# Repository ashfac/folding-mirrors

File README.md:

# Automatic Folding Mirrors schematics in KiCAD
## Schematics

## Board

## PCB

## PCBA

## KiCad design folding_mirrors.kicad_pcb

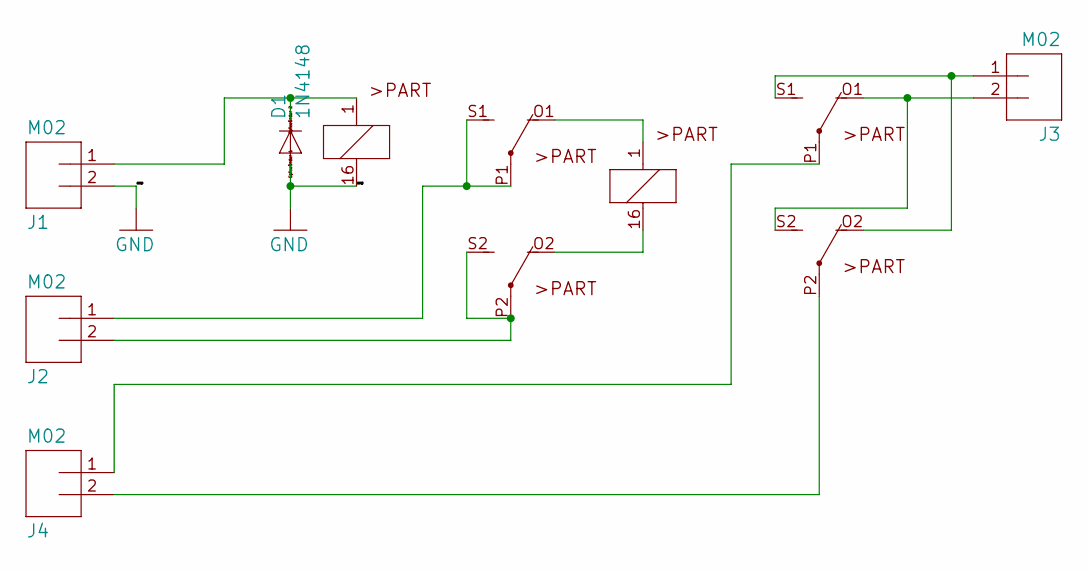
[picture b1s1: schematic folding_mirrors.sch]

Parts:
D1: 1N4148; DO35-7
J1, J2, J3, J4: M02
K1: HK19F
K2: NEC-EC2-EE2

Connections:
GND: D1.A, J1.2, K1.16 (2)
unnamed: D1.C, J1.1, K1.1
unnamed: J2.1, K1.P1, K1.S1 (S)
unnamed: J2.2, K1.P2, K1.S2 (S)
unnamed: J3.1, K2.O2 (O), K2.S1 (S)
unnamed: J3.2, K2.O1 (O), K2.S2 (S)
unnamed: J4.1, K2.P1
unnamed: J4.2, K2.P2
unnamed: K1.O1 (O), K2.1
unnamed: K1.O2 (O), K2.16 (2)

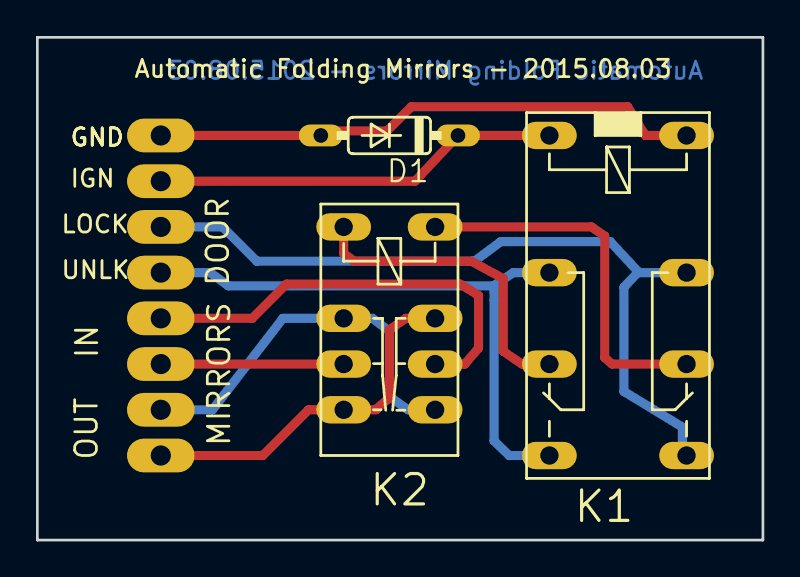
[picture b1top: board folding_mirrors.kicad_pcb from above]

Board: 2 copper layers, 40.3 x 27.9 mm, 7 parts (0 on the bottom side), 10 nets.

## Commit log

2019-06-09 add .gitignore
2019-06-09 add documents
2019-06-10 add pics to README.md
